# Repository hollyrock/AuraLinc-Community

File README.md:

# AuraLinc Community

[English](./README.en.md)

AuraLincのコミュニティサイトです。AuraLinc EcoCONNECTをオープンソースで公開しています。

## サイト構成

| セクション | 内容 |
| --- | --- |
| **ドキュメント** | はじめ方・チュートリアル・リポジトリ案内・FAQ |
| **ワークショップ資料** | ワークショップ用資料 |
| **コミュニティ広場** | アイデア・質問・提案（GitHub Discussions / giscus） |

- **サイト:** https://hollyrock.github.io/AuraLinc-Community/
- **Discussions:** https://github.com/hollyrock/AuraLinc-Community/discussions

```text
AuraLinc-Community/
├── docs/                   # Github Pages用ソース
│   ├── index.md
│   ├── community/          # アイデア・質問・提案
│   ├── docs/               # マニュアル・FAQ等
│   ├── en/                 # 英語表示用
│   ├── public/             # ロゴや共通オブジェクト
│   └── steam/              # ワークショップ用資料
├── firmware/
│   ├── main/               # EcoCONNECT制御コード
│   └── pico2/
│       ├── release/            # Pico2 イメージ
│       └── auralinc_c_modules/ # Pico2 F/Wコード
├── hardware/
│   ├── main-board/         # メイン基板回路データ
│   │   └── libs/           # KiCADライブラリ
│   └── steam-board/        # STEAMセンサー基板回路データ
│       └── libs/           # KiCADライブラリ
└── site/                   # サイト本体
```

## ライセンス

本プロジェクトはコンポーネントごとに複数のライセンスが存在します。

- **ハードウェア デザイン** (`/hardware/`): [CERN-OHL-P-2.0](hardware/LICENSE-CERN-OHL-P.txt)
- **ファームウェア ソースコード** (`/firmware/`): [MIT License](firmware/LICENSE-MIT.txt)
- **ドキュメント & メディア** (`/docs/`): [CC-BY-4.0](docs/LICENSE-CC-BY.txt)

各フォルダに存在する`LICENSE`ファイルを参照してください。

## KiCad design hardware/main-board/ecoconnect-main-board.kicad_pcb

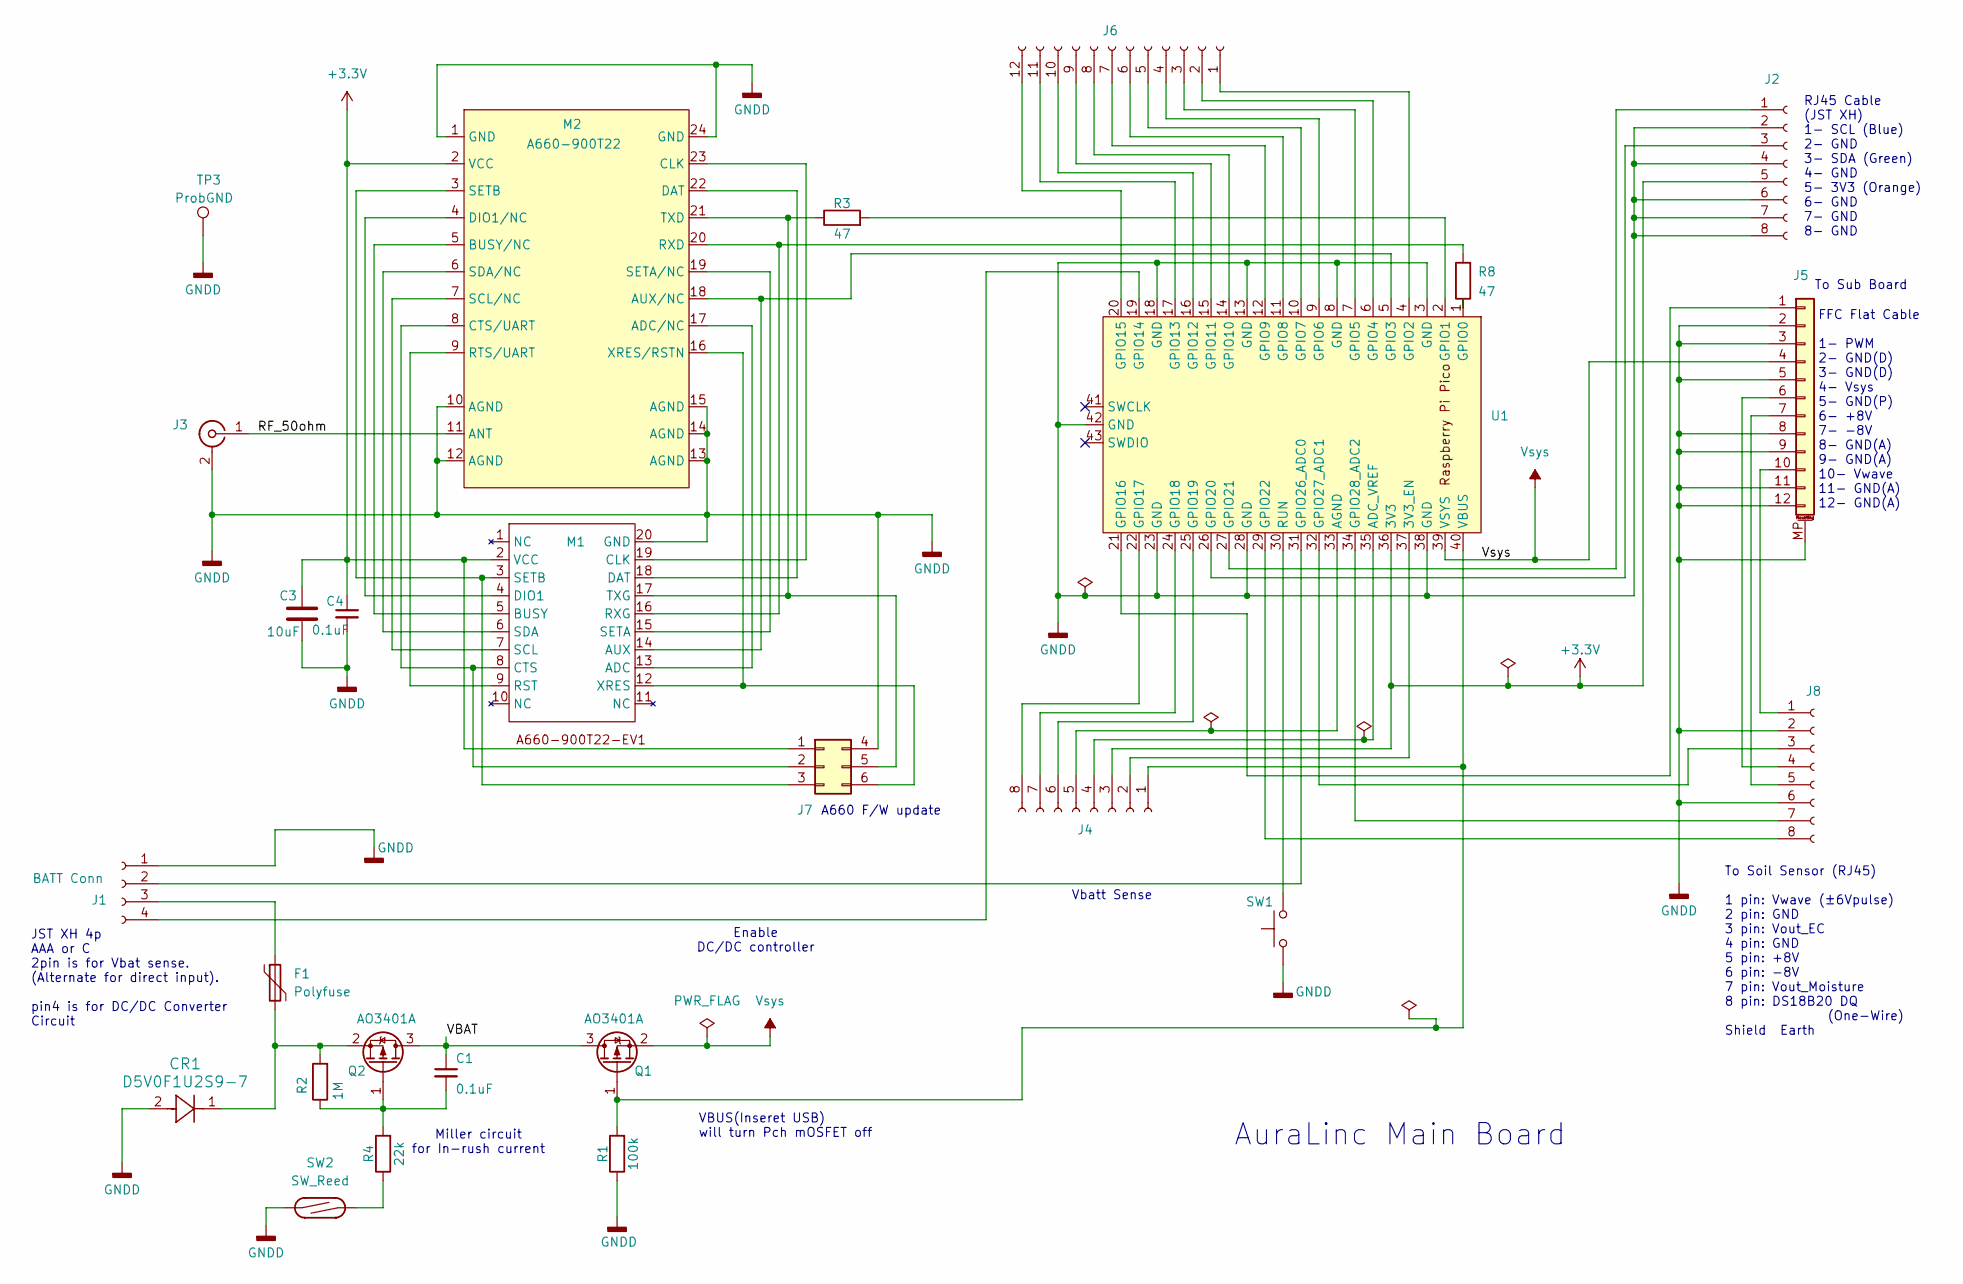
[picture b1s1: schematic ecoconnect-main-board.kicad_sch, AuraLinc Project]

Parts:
C1, C4: 0.1uF; C_0603_1608Metric_Pad1.08x0.95mm_HandSolder
C3: 10uF; C_0805_2012Metric_Pad1.18x1.45mm_HandSolder
CR1: D5V0F1U2S9-7; D5V0F1U2S9
F1: Polyfuse; FUS_MINISMDC075F_TYCO_TYC
J1: BATT Conn; JST_XH_B4B-XH-A_1x04_P2.50mm_Vertical
J2, J8: Conn_01x08_Socket; JST_XH_B8B-XH-AM_1x08_P2.50mm_Vertical
J3: Conn_Coaxial; SMA_Samtec_SMA-J-P-H-ST-EM1_EdgeMount
J4: Conn_01x08_Socket; PinHeader_1x08_P2.54mm_Vertical
J5: Conn_01x12_MountingPin; TE_1-84952-2_1x12-1MP_P1.0mm_Horizontal
J6: Conn_01x12_Socket; PinHeader_1x12_P2.54mm_Vertical
J7: Conn_02x03_Top_Bottom; PinSocket_2x03_P2.54mm_Vertical
M1: A660-900T22-EV1
M2: A660-900T22
Q1, Q2: AO3401A; SOT-23
R1: 100k; R_0805_2012Metric_Pad1.20x1.40mm_HandSolder
R2: 1M; R_0805_2012Metric_Pad1.20x1.40mm_HandSolder
R3, R8: 47; R_0805_2012Metric_Pad1.20x1.40mm_HandSolder
R4: 22k; R_0805_2012Metric_Pad1.20x1.40mm_HandSolder
SW1: SW_Omron_B3FS; SW_SPST_Omron_B3FS-100xP
SW2: SW_Reed; JST_XH_B2B-XH-AM_1x02_P2.50mm_Vertical
TP3: ProbGND; TestPoint_Keystone_5015_Micro_Mini
U1: RPi_Pico_SMD_TH

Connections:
+3.3V: C3.1, C4.1, J2.5, J4.3, J7.1, M1.2 (VCC), M2.2 (VCC), U1.36 (3V3)
/RF_50ohm: J3.1 (In), M2.11 (ANT)
/VBAT: C1.1, Q1.3 (D), Q2.3 (D)
GNDD: C3.2, C4.2, CR1.2, J1.1, J2.2, J2.4, J2.6, J2.7, J2.8, J3.2 (Ext), J5.2, J5.3, J5.5, J5.8, J5.9, J5.11, J5.12, J5.MP (MountPin), J7.4, J8.2, J8.6, M1.20 (GND), M2.1 (GND), M2.10 (AGND), M2.12 (AGND), M2.13 (AGND), M2.14 (AGND), M2.15 (AGND), M2.24 (GND), R1.1, SW1.1, SW2.1, TP3.1, U1.3 (GND), U1.8 (GND), U1.13 (GND), U1.18 (GND), U1.23 (GND), U1.28 (GND), U1.38 (GND), U1.42 (GND)
unnamed: J1.2, U1.31 (GPIO26_ADC0)
unnamed: F1.1, J1.3
unnamed: J1.4, U1.19 (GPIO14)
unnamed: J2.1, U1.27 (GPIO21)
unnamed: J2.3, U1.26 (GPIO20)
unnamed: J4.1, Q1.1 (G), R1.2, U1.40 (VBUS)
unnamed: J4.2, U1.37 (3V3_EN)
unnamed: J4.4, U1.35 (ADC_VREF)
unnamed: J4.5, U1.33 (AGND)
unnamed: J4.6, U1.25 (GPIO19)
unnamed: J4.7, U1.24 (GPIO18)
unnamed: J4.8, U1.22 (GPIO17)
unnamed: J5.1, U1.21 (GPIO16)
unnamed: J5.6, J8.4
unnamed: J5.7, J8.5
unnamed: J5.10, J8.1
unnamed: J6.1, U1.4 (GPIO2)
unnamed: J6.2, U1.6 (GPIO4)
unnamed: J6.3, U1.7 (GPIO5)
unnamed: J6.4, U1.9 (GPIO6)
unnamed: J6.5, U1.10 (GPIO7)
unnamed: J6.6, U1.11 (GPIO8)
unnamed: J6.7, U1.12 (GPIO9)
unnamed: J6.8, U1.14 (GPIO10)
unnamed: J6.9, U1.15 (GPIO11)
unnamed: J6.10, U1.16 (GPIO12)
unnamed: J6.11, U1.17 (GPIO13)
unnamed: J6.12, U1.20 (GPIO15)
unnamed: J7.2, M1.8 (CTS), M2.8 (CTS/UART)
unnamed: J7.3, M1.3 (SETB), M2.3 (SETB)
unnamed: J7.5, M1.17 (TXG), M2.21 (TXD), R3.1
unnamed: J7.6, M1.12 (XRES), M2.16 (XRES/RSTN)
unnamed: J8.3, U1.32 (GPIO27_ADC1)
unnamed: J8.7, U1.34 (GPIO28_ADC2)
unnamed: J8.8, U1.29 (GPIO22)
unnamed: M1.13 (ADC), M2.17 (ADC/NC)
unnamed: M1.14 (AUX), M2.18 (AUX/NC), U1.5 (GPIO3)
unnamed: M1.5 (BUSY), M2.5 (BUSY/NC)
unnamed: M1.19 (CLK), M2.23 (CLK)
unnamed: M1.18 (DAT), M2.22 (DAT)
unnamed: M1.4 (DIO1), M2.4 (DIO1/NC)
unnamed: M1.9 (RST), M2.9 (RTS/UART)
unnamed: M1.16 (RXG), M2.20 (RXD), R8.2
unnamed: M1.7 (SCL), M2.7 (SCL/NC)
unnamed: M1.6 (SDA), M2.6 (SDA/NC)
unnamed: M1.15 (SETA), M2.19 (SETA/NC)
unnamed: C1.2, Q2.1 (G), R2.1, R4.2
unnamed: CR1.1, F1.2, Q2.2 (S), R2.2
unnamed: R4.1, SW2.2
unnamed: R8.1, U1.1 (GPIO0)
unnamed: R3.2, U1.2 (GPIO1)
unnamed: SW1.2, U1.30 (RUN)
Vsys: J5.4, Q1.2 (S), U1.39 (VSYS)

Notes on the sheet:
To Soil Sensor (RJ45) 1 pin: Vwave (±6Vpulse) 2 pin: GND 3 pin: Vout_EC 4 pin: GND 5 pin: +8V 6 pin: -8V 7 pin: Vout_Moisture 8 pin: DS18B20 DQ (One-Wire) Shield Earth
FFC Flat Cable 1- PWM 2- GND(D) 3- GND(D) 4- Vsys 5- GND(P) 6- +8V 7- -8V 8- GND(A) 9- GND(A) 10- Vwave 11- GND(A) 12- GND(A)
To Sub Board
A660 F/W update
AuraLinc Main Board
Miller circuit for In-rush current
VBUS(Inseret USB) will turn Pch mOSFET off
Enable DC/DC controller
Vbatt Sense
RJ45 Cable (JST XH) 1- SCL (Blue) 2- GND 3- SDA (Green) 4- GND 5- 3V3 (Orange) 6- GND 7- GND 8- GND
JST XH 4p AAA or C 2pin is for Vbat sense. (Alternate for direct input). pin4 is for DC/DC Converter Circuit

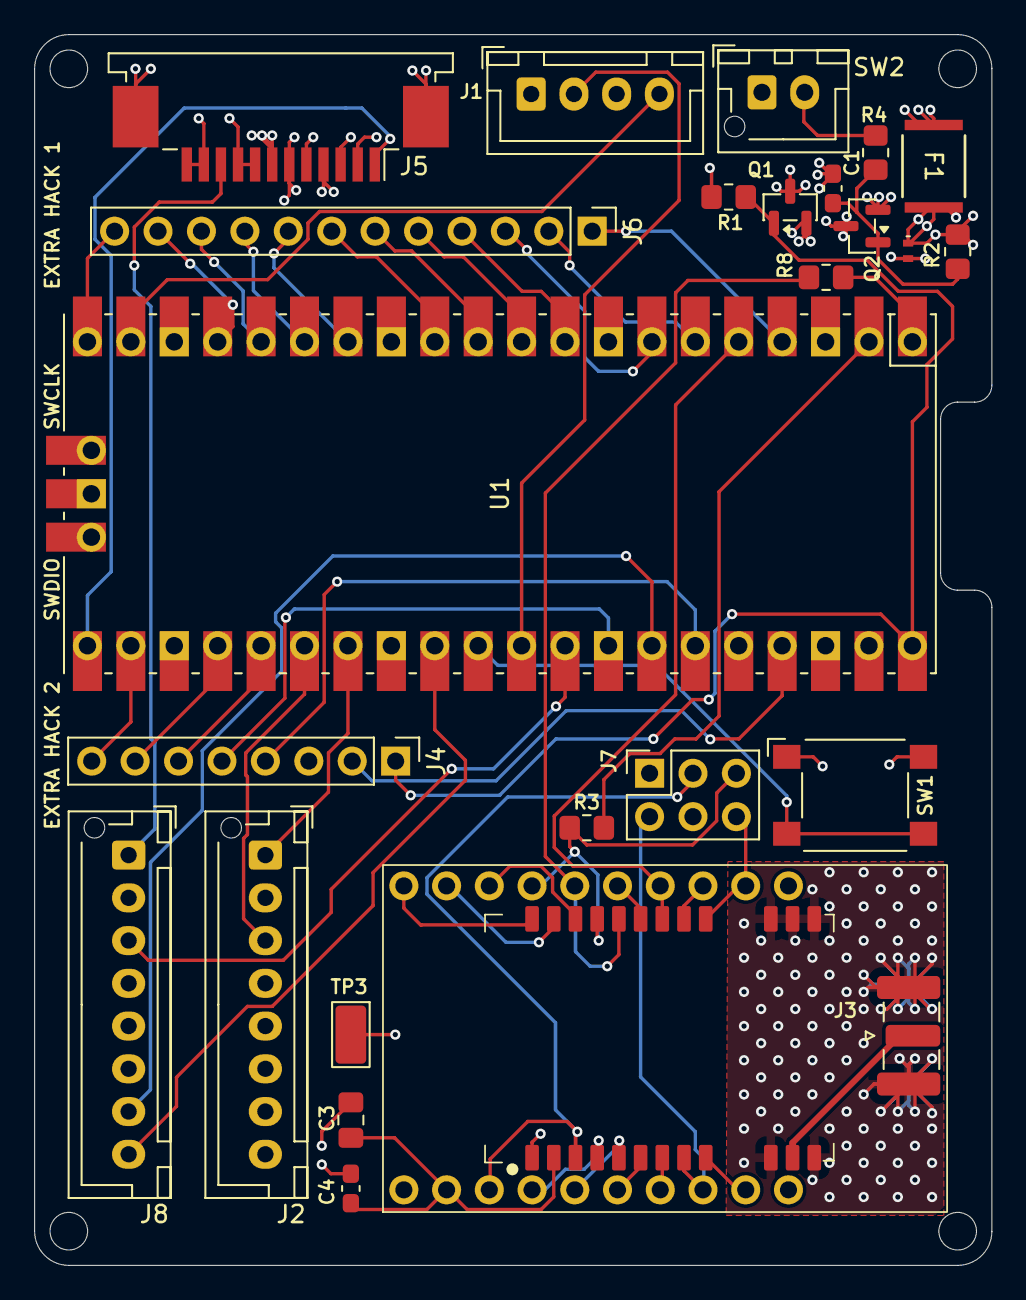
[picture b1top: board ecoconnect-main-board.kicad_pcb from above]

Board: 4 copper layers, 56.0 x 72.0 mm, 26 parts (0 on the bottom side), 57 nets.

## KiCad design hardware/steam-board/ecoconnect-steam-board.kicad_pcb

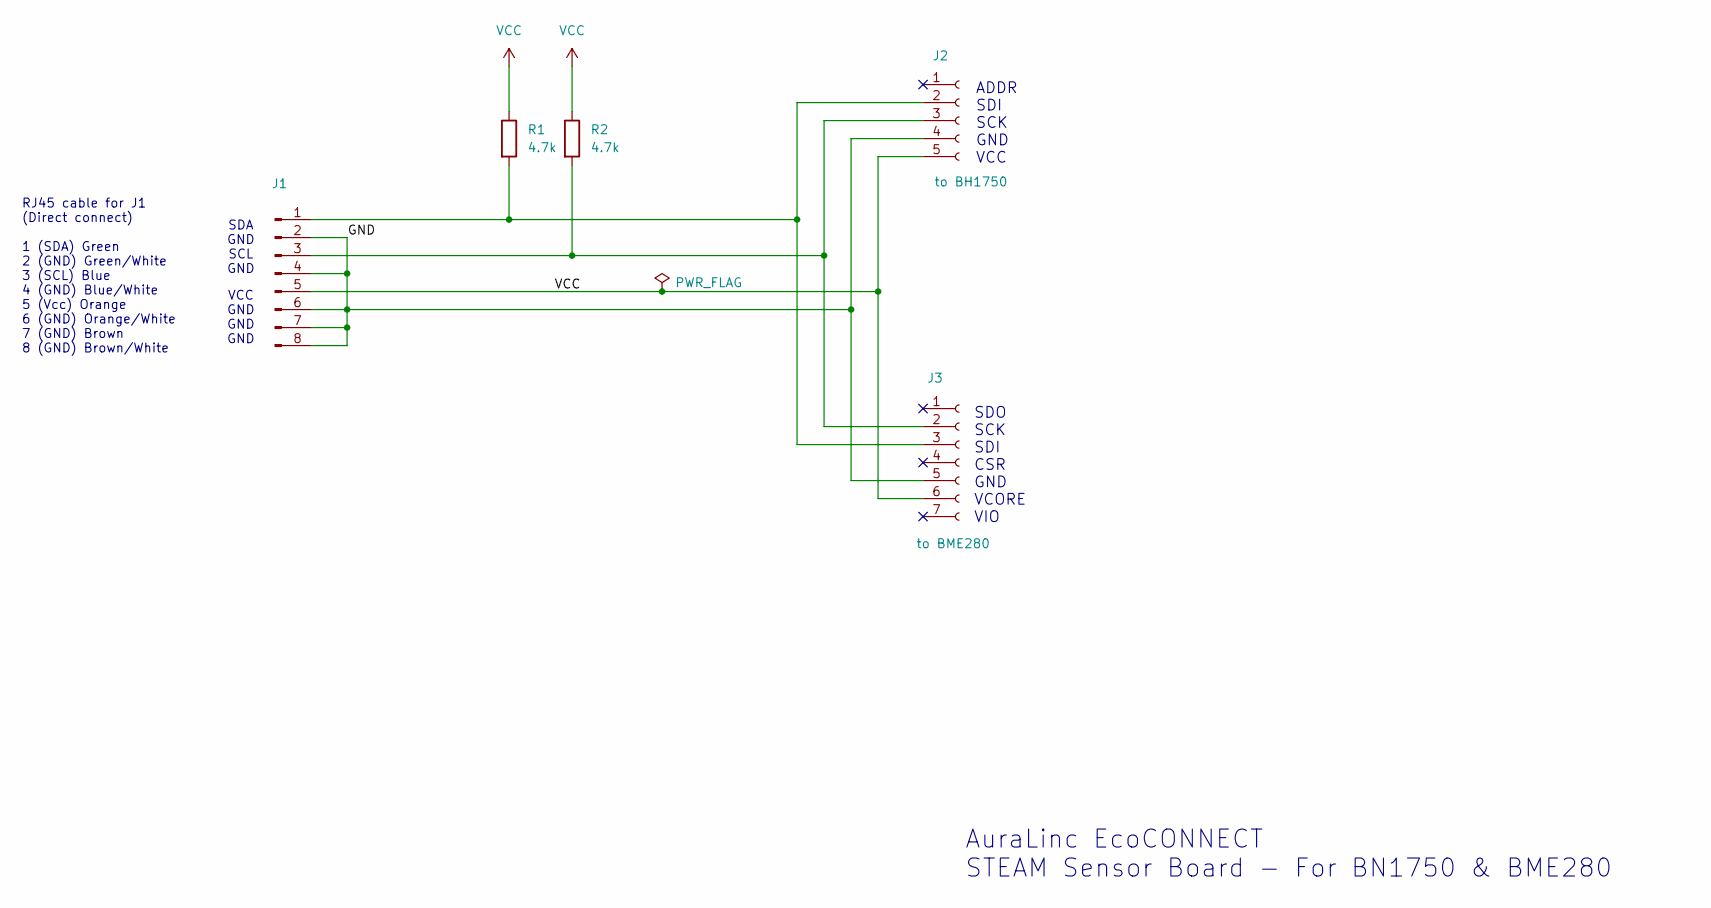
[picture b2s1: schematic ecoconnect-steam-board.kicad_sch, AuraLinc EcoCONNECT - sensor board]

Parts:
J1: Conn_01x08_Pin; 8 through hole -zigzag
J2: to BH1750; PinHeader_1x05_P2.54mm_Vertical
J3: to BME280; PinHeader_1x07_P2.54mm_Vertical
R1, R2: 4.7k; R_0805_2012Metric

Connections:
/GND: J1.2, J1.4, J1.6, J1.7, J1.8, J2.4, J3.5
unnamed: J1.1, J2.2, J3.3, R1.2
unnamed: J1.3, J2.3, J3.2, R2.2
VCC: J1.5, J2.5, J3.6, R1.1, R2.1

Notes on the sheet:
VCC GND GND GND
AuraLinc EcoCONNECT STEAM Sensor Board - For BN1750 & BME280
SDA GND SCL GND
ADDR SDI SCK GND VCC
RJ45 cable for J1 (Direct connect) 1 (SDA) Green 2 (GND) Green/White 3 (SCL) Blue 4 (GND) Blue/White 5 (Vcc) Orange 6 (GND) Orange/White 7 (GND) Brown 8 (GND) Brown/White
SDO SCK SDI CSR GND VCORE VIO

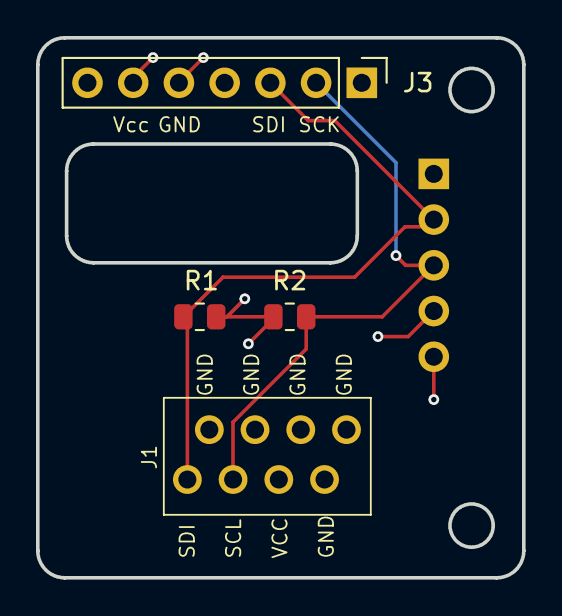
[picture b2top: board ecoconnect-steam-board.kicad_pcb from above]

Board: 4 copper layers, 27.0 x 30.0 mm, 5 parts (1 on the bottom side), 4 nets.
